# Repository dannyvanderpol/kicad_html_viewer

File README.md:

# kicad_html_viewer
Viewer for viewing KiCad designs in a HTML page

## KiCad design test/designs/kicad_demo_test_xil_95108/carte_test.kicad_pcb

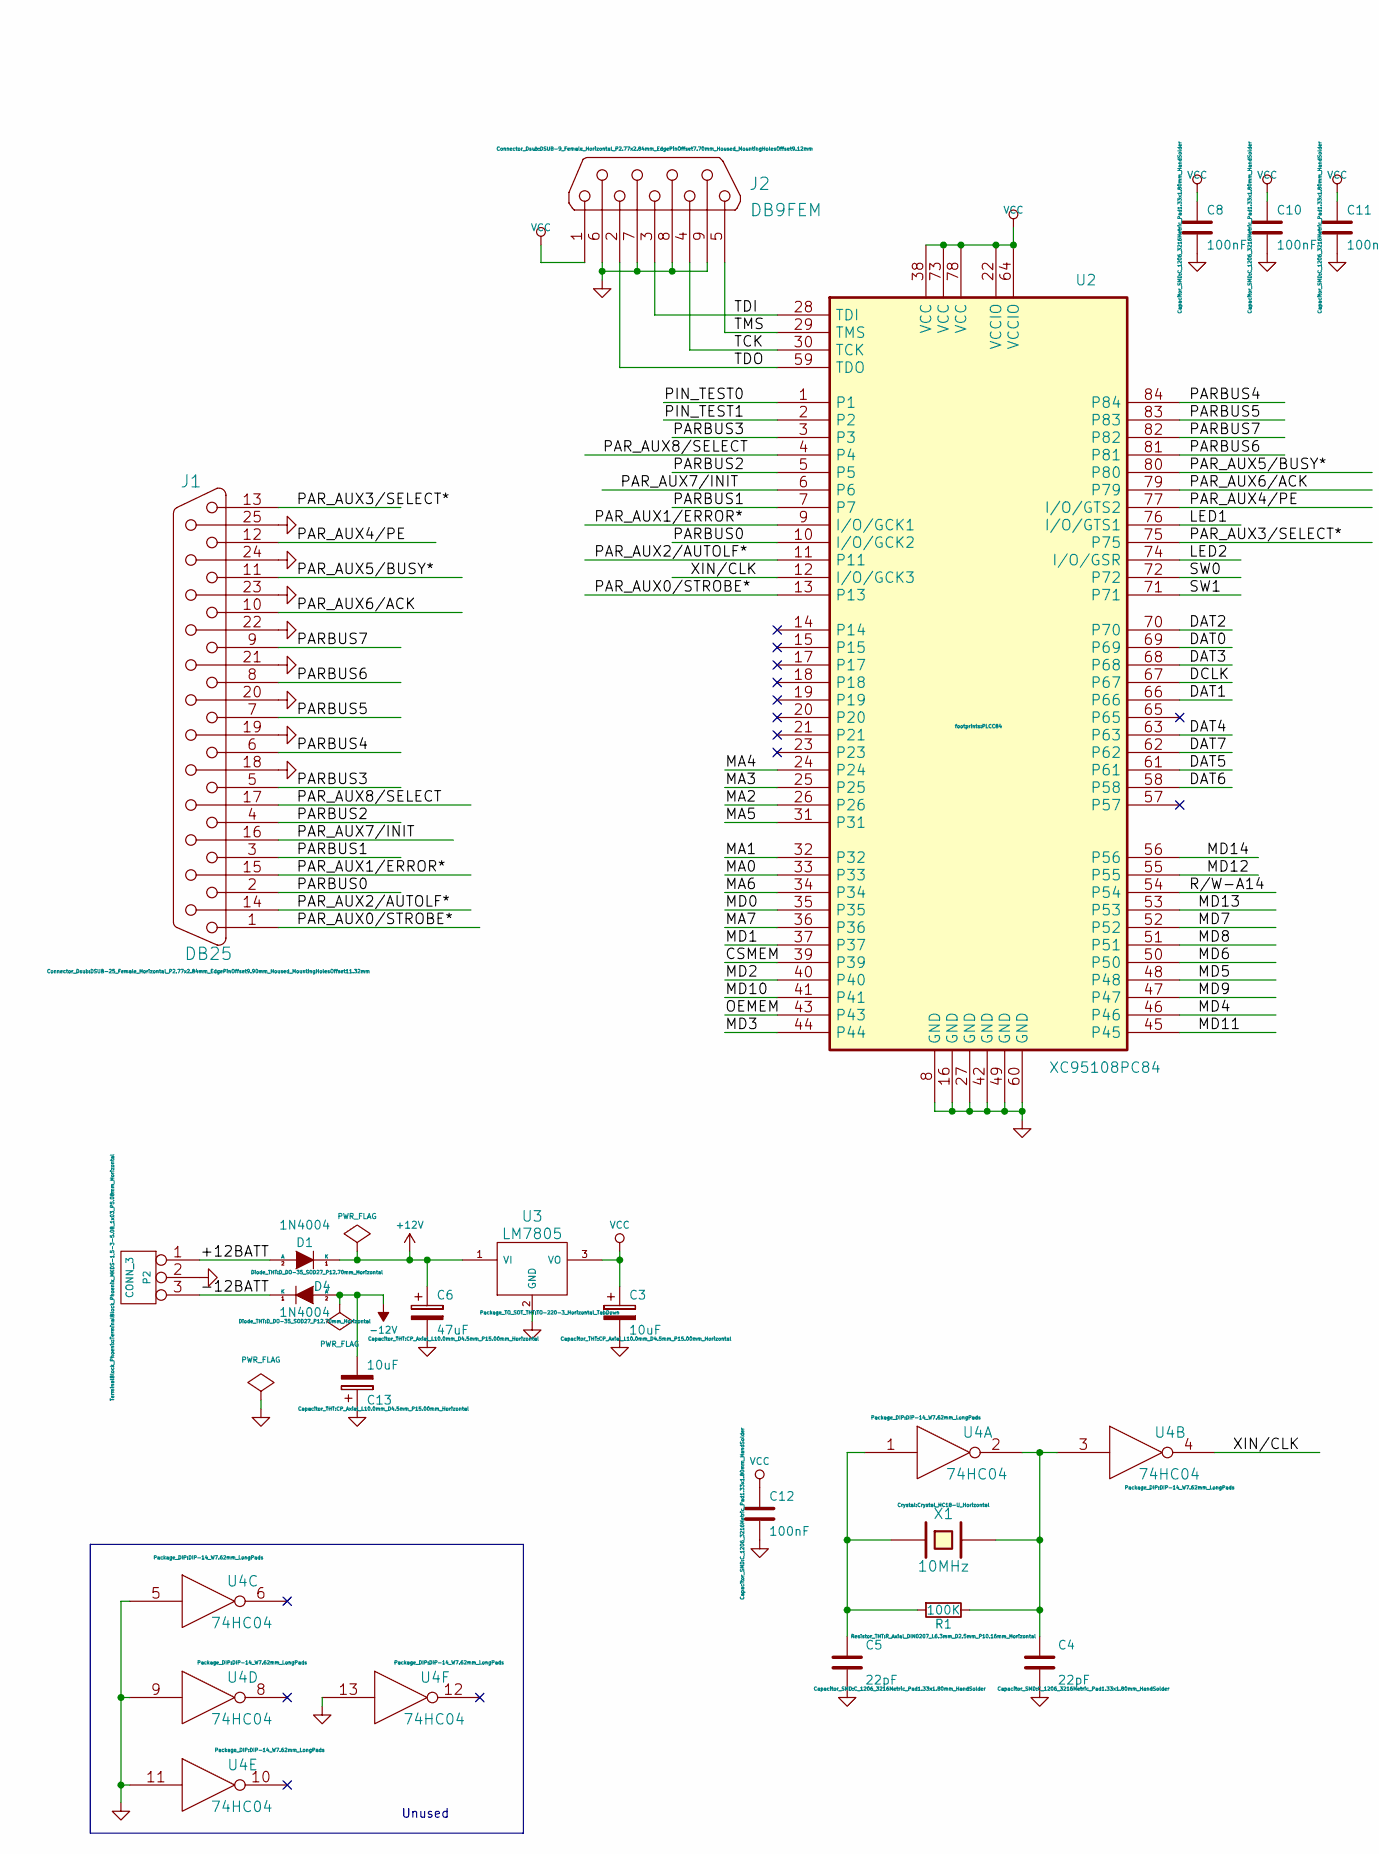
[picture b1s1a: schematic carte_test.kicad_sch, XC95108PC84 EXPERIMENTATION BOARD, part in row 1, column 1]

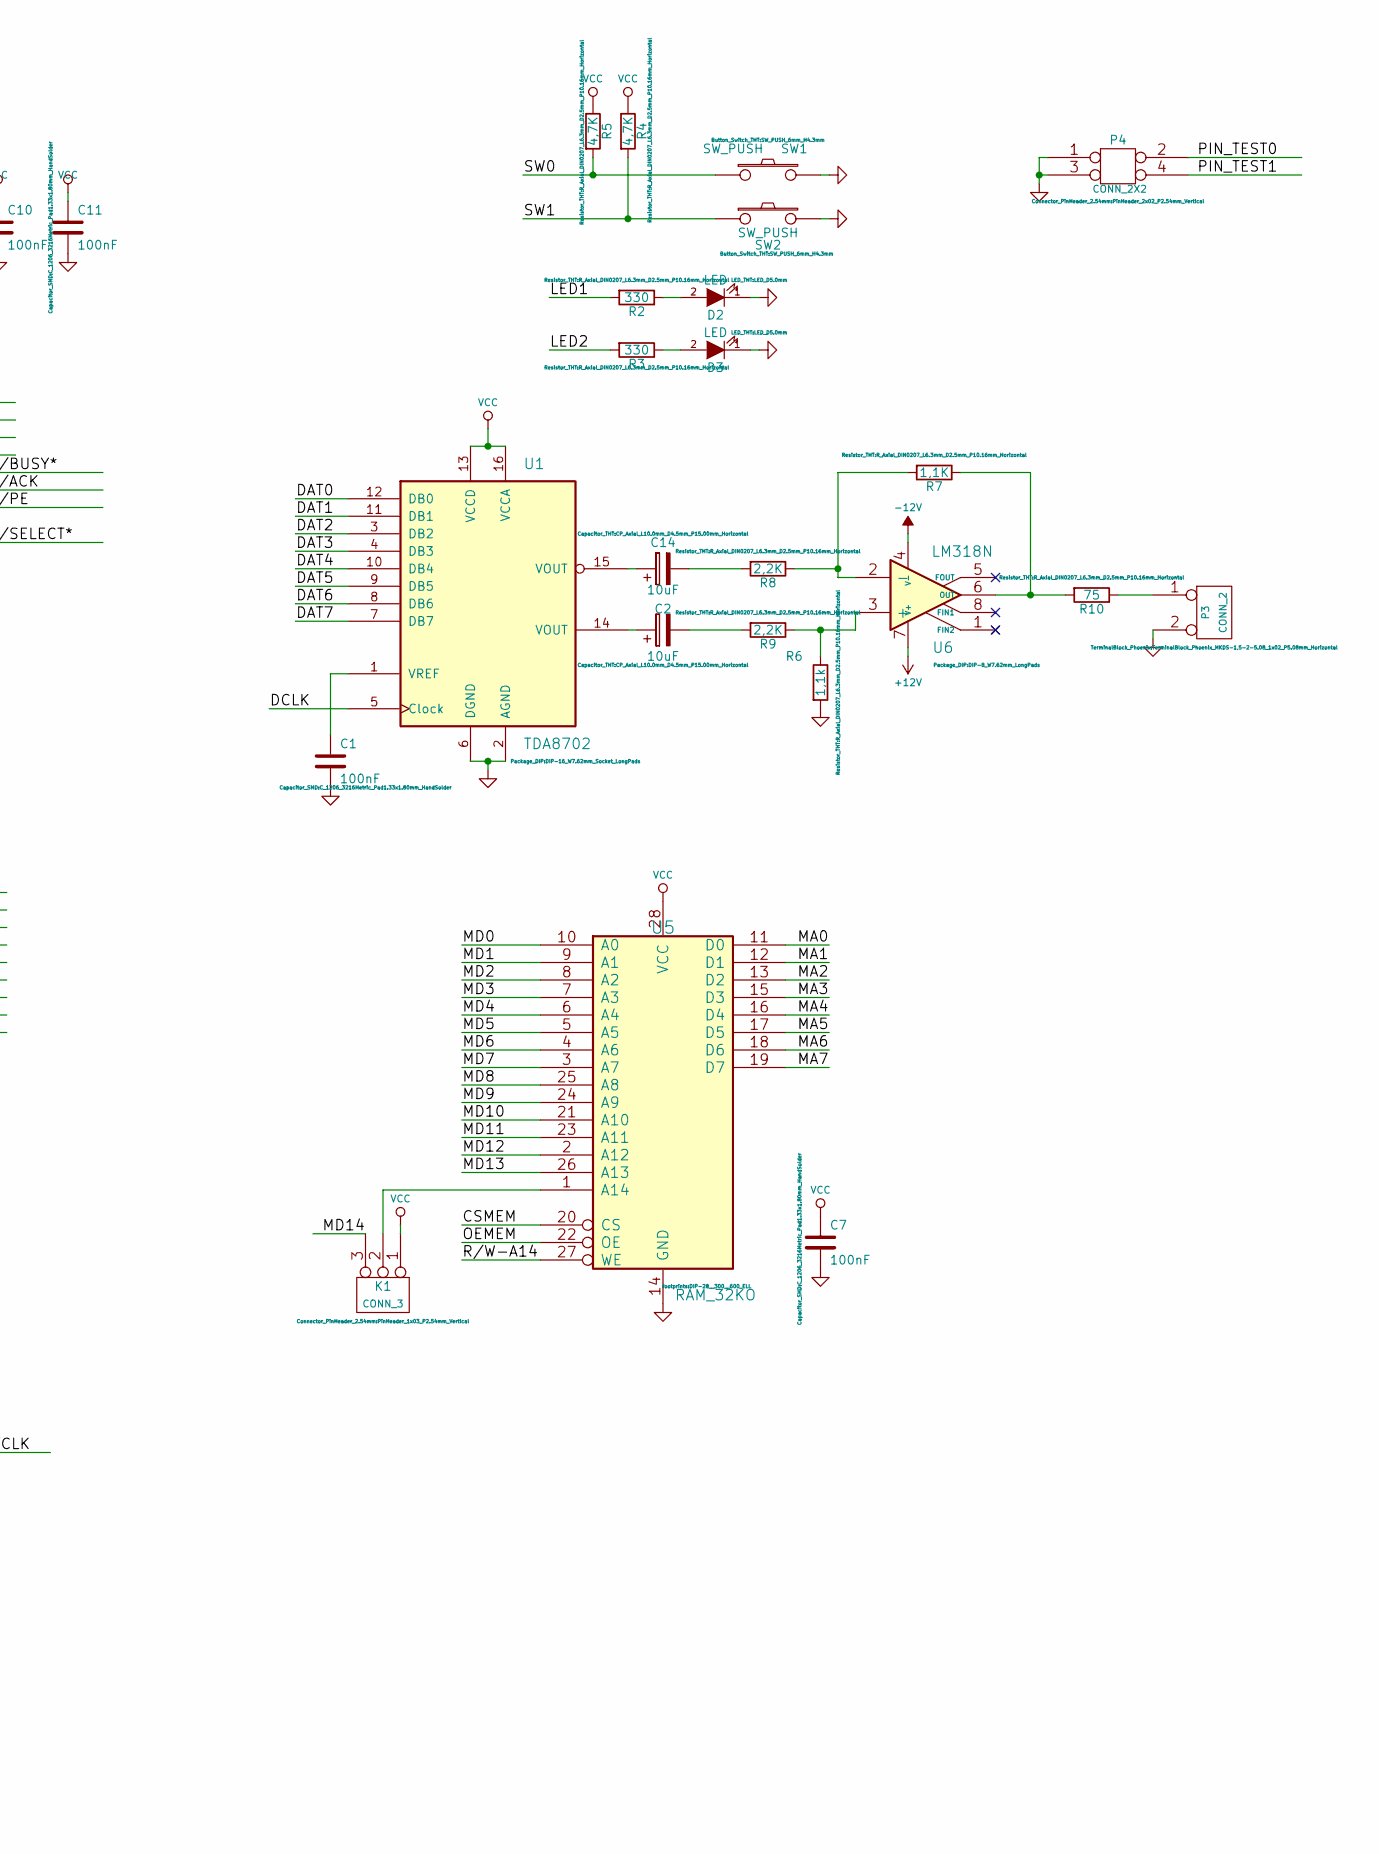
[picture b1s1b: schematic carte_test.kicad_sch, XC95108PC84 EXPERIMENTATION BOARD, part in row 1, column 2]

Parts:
C1, C7, C8, C10, C11, C12: 100nF; C_1206_3216Metric_Pad1.33x1.80mm_HandSolder
C2, C3, C13, C14: 10uF; CP_Axial_L10.0mm_D4.5mm_P15.00mm_Horizontal
C4, C5: 22pF; C_1206_3216Metric_Pad1.33x1.80mm_HandSolder
C6: 47uF; CP_Axial_L10.0mm_D4.5mm_P15.00mm_Horizontal
D1, D4: 1N4004; D_DO-35_SOD27_P12.70mm_Horizontal
D2, D3: LED; LED_D5.0mm
J1: DB25; DSUB-25_Female_Horizontal_P2.77x2.84mm_EdgePinOffset9.90mm_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
J2: DB9FEM; DSUB-9_Female_Horizontal_P2.77x2.84mm_EdgePinOffset7.70mm_H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
K1: CONN_3; PinHeader_1x03_P2.54mm_Vertical
P2: CONN_3; TerminalBlock_Phoenix_MKDS-1,5-3-5.08_1x03_P5.08mm_Horizont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
P3: CONN_2; TerminalBlock_Phoenix_MKDS-1,5-2-5.08_1x02_P5.08mm_Horizont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
P4: CONN_2X2; PinHeader_2x02_P2.54mm_Vertical
R1: 100K; R_Axial_DIN0207_L6.3mm_D2.5mm_P10.16mm_Horizontal
R2, R3: 330; R_Axial_DIN0207_L6.3mm_D2.5mm_P10.16mm_Horizontal
R4, R5: 4,7K; R_Axial_DIN0207_L6.3mm_D2.5mm_P10.16mm_Horizontal
R6: 1,1k; R_Axial_DIN0207_L6.3mm_D2.5mm_P10.16mm_Horizontal
R7: 1,1K; R_Axial_DIN0207_L6.3mm_D2.5mm_P10.16mm_Horizontal
R8, R9: 2,2K; R_Axial_DIN0207_L6.3mm_D2.5mm_P10.16mm_Horizontal
R10: 75; R_Axial_DIN0207_L6.3mm_D2.5mm_P10.16mm_Horizontal
SW1, SW2: SW_PUSH; SW_PUSH_6mm_H4.3mm
U1: TDA8702; DIP-16_W7.62mm_Socket_LongPads
U2: XC95108PC84; PLCC84
U3: LM7805; TO-220-3_Horizontal_TabDown
U4: 74HC04; DIP-14_W7.62mm_LongPads
U5: RAM_32KO; DIP-28__300__600_ELL
U6: LM318N; DIP-8_W7.62mm_LongPads
X1: 10MHz; Crystal_HC18-U_Horizontal

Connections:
+12V: C6.1, D1.1 (K), U3.1 (VI), U6.7 (V+)
-12V: C13.2, D4.2 (A), U6.4 (V-)
/+12BATT: D1.2 (A), P2.1
/-12BATT: D4.1 (K), P2.3
/CSMEM: U2.39, U5.20 (CS)
/DAT0: U1.12 (DB0), U2.69
/DAT1: U1.11 (DB1), U2.66
/DAT2: U1.3 (DB2), U2.70
/DAT3: U1.4 (DB3), U2.68
/DAT4: U1.10 (DB4), U2.63
/DAT5: U1.9 (DB5), U2.61
/DAT6: U1.8 (DB6), U2.58
/DAT7: U1.7 (DB7), U2.62
/DCLK: U1.5 (Clock), U2.67
/LED1: R2.2, U2.76 (I/O/GTS1)
/LED2: R3.2, U2.74 (I/O/GSR)
/MA0: U2.33, U5.11 (D0)
/MA1: U2.32, U5.12 (D1)
/MA2: U2.26, U5.13 (D2)
/MA3: U2.25, U5.15 (D3)
/MA4: U2.24, U5.16 (D4)
/MA5: U2.31, U5.17 (D5)
/MA6: U2.34, U5.18 (D6)
/MA7: U2.36, U5.19 (D7)
/MD0: U2.35, U5.10 (A0)
/MD1: U2.37, U5.9 (A1)
/MD2: U2.40, U5.8 (A2)
/MD3: U2.44, U5.7 (A3)
/MD4: U2.46, U5.6 (A4)
/MD5: U2.48, U5.5 (A5)
/MD6: U2.50, U5.4 (A6)
/MD7: U2.52, U5.3 (A7)
/MD8: U2.51, U5.25 (A8)
/MD9: U2.47, U5.24 (A9)
/MD10: U2.41, U5.21 (A10)
/MD11: U2.45, U5.23 (A11)
/MD12: U2.55, U5.2 (A12)
/MD13: U2.53, U5.26 (A13)
/MD14: K1.3, U2.56
/OEMEM: U2.43, U5.22 (OE)
/PARBUS0: J1.2, U2.10 (I/O/GCK2)
/PARBUS1: J1.3, U2.7
/PARBUS2: J1.4, U2.5
/PARBUS3: J1.5, U2.3
/PARBUS4: J1.6, U2.84
/PARBUS5: J1.7, U2.83
/PARBUS6: J1.8, U2.81
/PARBUS7: J1.9, U2.82
/PAR_AUX0/STROBE*: J1.1, U2.13
/PAR_AUX1/ERROR*: J1.15, U2.9 (I/O/GCK1)
/PAR_AUX2/AUTOLF*: J1.14, U2.11
/PAR_AUX3/SELECT*: J1.13, U2.75
/PAR_AUX4/PE: J1.12, U2.77 (I/O/GTS2)
/PAR_AUX5/BUSY*: J1.11, U2.80
/PAR_AUX6/ACK: J1.10, U2.79
/PAR_AUX7/INIT: J1.16, U2.6
/PAR_AUX8/SELECT: J1.17, U2.4
/PIN_TEST0: P4.2, U2.1
/PIN_TEST1: P4.4, U2.2
/R/W-A14: U2.54, U5.27 (WE)
/SW0: R5.2, SW1.1, U2.72
/SW1: R4.2, SW2.1, U2.71
/TCK: J2.4, U2.30 (TCK)
/TDI: J2.3, U2.28 (TDI)
/TDO: J2.2, U2.59 (TDO)
/TMS: J2.5, U2.29 (TMS)
/XIN/CLK: U2.12 (I/O/GCK3), U4.4
GND: C1.2, C3.2, C4.2, C5.2, C6.2, C7.2, C8.2, C10.2, C11.2, C12.2, C13.1, D2.1 (K), D3.1 (K), J1.18, J1.19, J1.20, J1.21, J1.22, J1.23, J1.24, J1.25, J2.6, J2.7, J2.8, J2.9, P2.2 (PM), P3.2 (PM), P4.1, P4.3, R6.2, SW1.2, SW2.2, U1.2 (AGND), U1.6 (DGND), U2.8 (GND), U2.16 (GND), U2.27 (GND), U2.42 (GND), U2.49 (GND), U2.60 (GND), U3.2 (GND), U4.5, U4.7 (GND), U4.9, U4.11, U4.13, U5.14 (GND)
unnamed: C2.1, U1.14 (VOUT)
unnamed: C2.2, R9.2
unnamed: C4.1, R1.1, U4.2, U4.3, X1.2
unnamed: C5.1, R1.2, U4.1, X1.1
unnamed: C14.1, U1.15 (VOUT)
unnamed: C14.2, R8.2
unnamed: D2.2 (A), R2.1
unnamed: D3.2 (A), R3.1
unnamed: K1.2 (PM), U5.1 (A14)
unnamed: P3.1, R10.1
unnamed: C1.1, U1.1 (VREF)
unnamed: R6.1, R9.1, U6.3 (+)
unnamed: R7.2, R8.1, U6.2 (-)
unnamed: R7.1, R10.2, U6.6 (OUT)
VCC: C3.1, C7.1, C8.1, C10.1, C11.1, C12.1, J2.1, K1.1, R4.1, R5.1, U1.13 (VCCD), U1.16 (VCCA), U2.22 (VCCIO), U2.38 (VCC), U2.64 (VCCIO), U2.73 (VCC), U2.78 (VCC), U3.3 (VO), U4.14 (VCC), U5.28 (VCC)

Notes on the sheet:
Unused

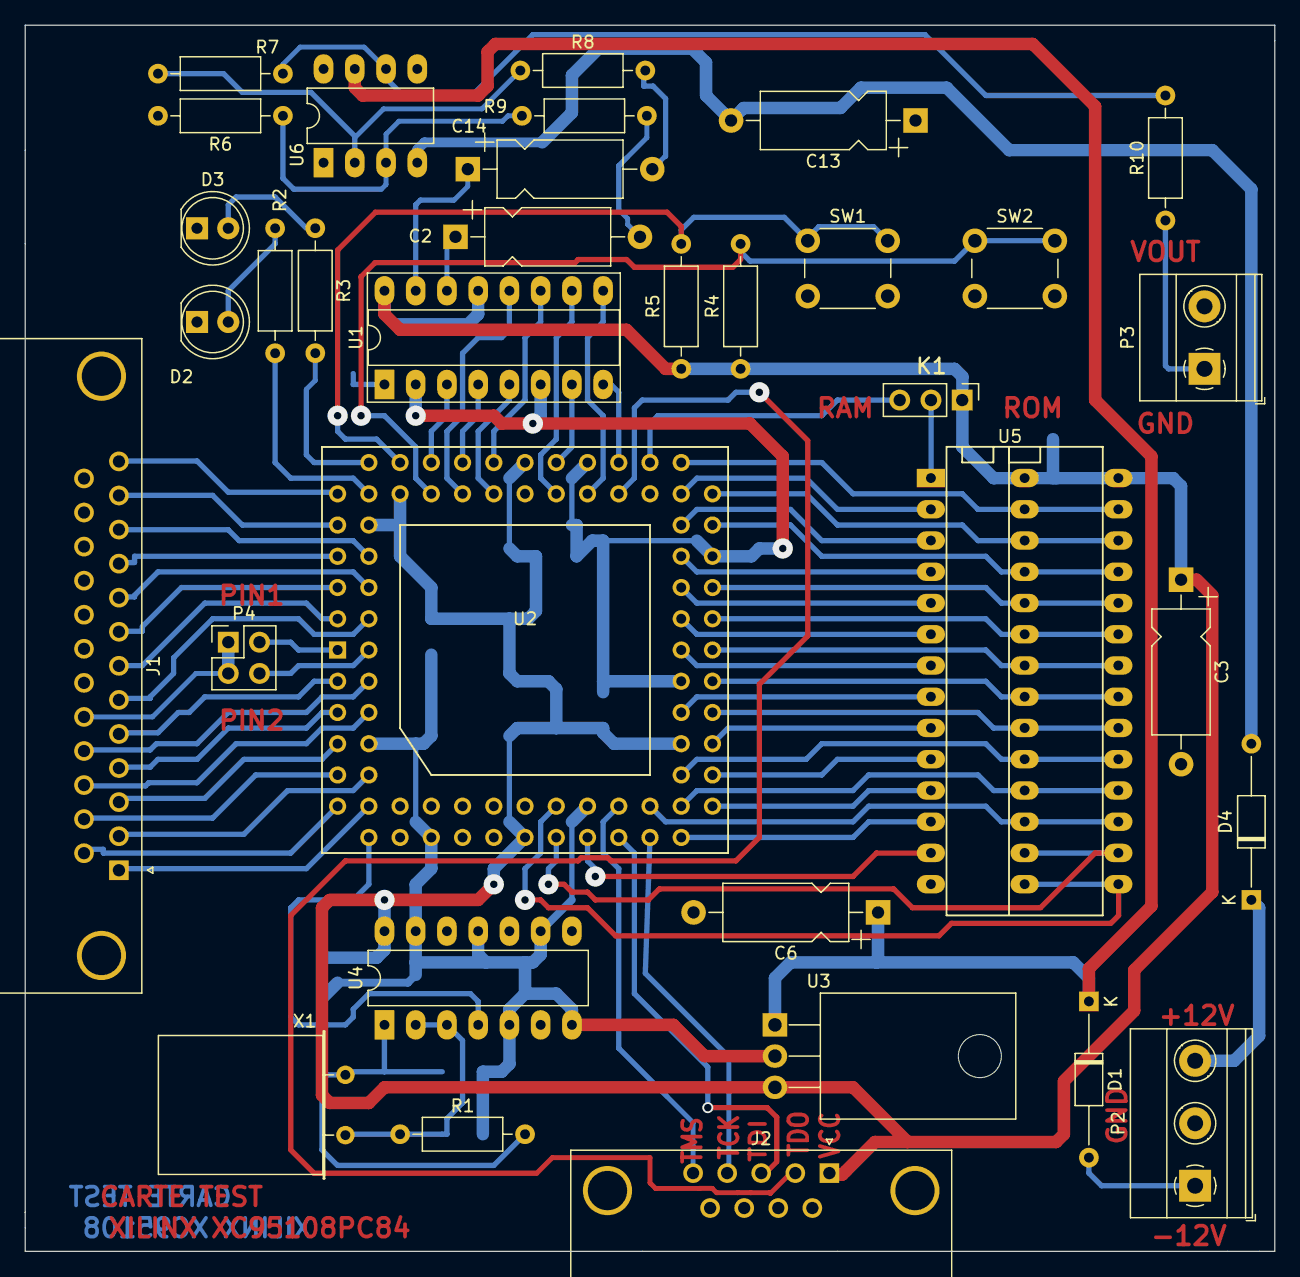
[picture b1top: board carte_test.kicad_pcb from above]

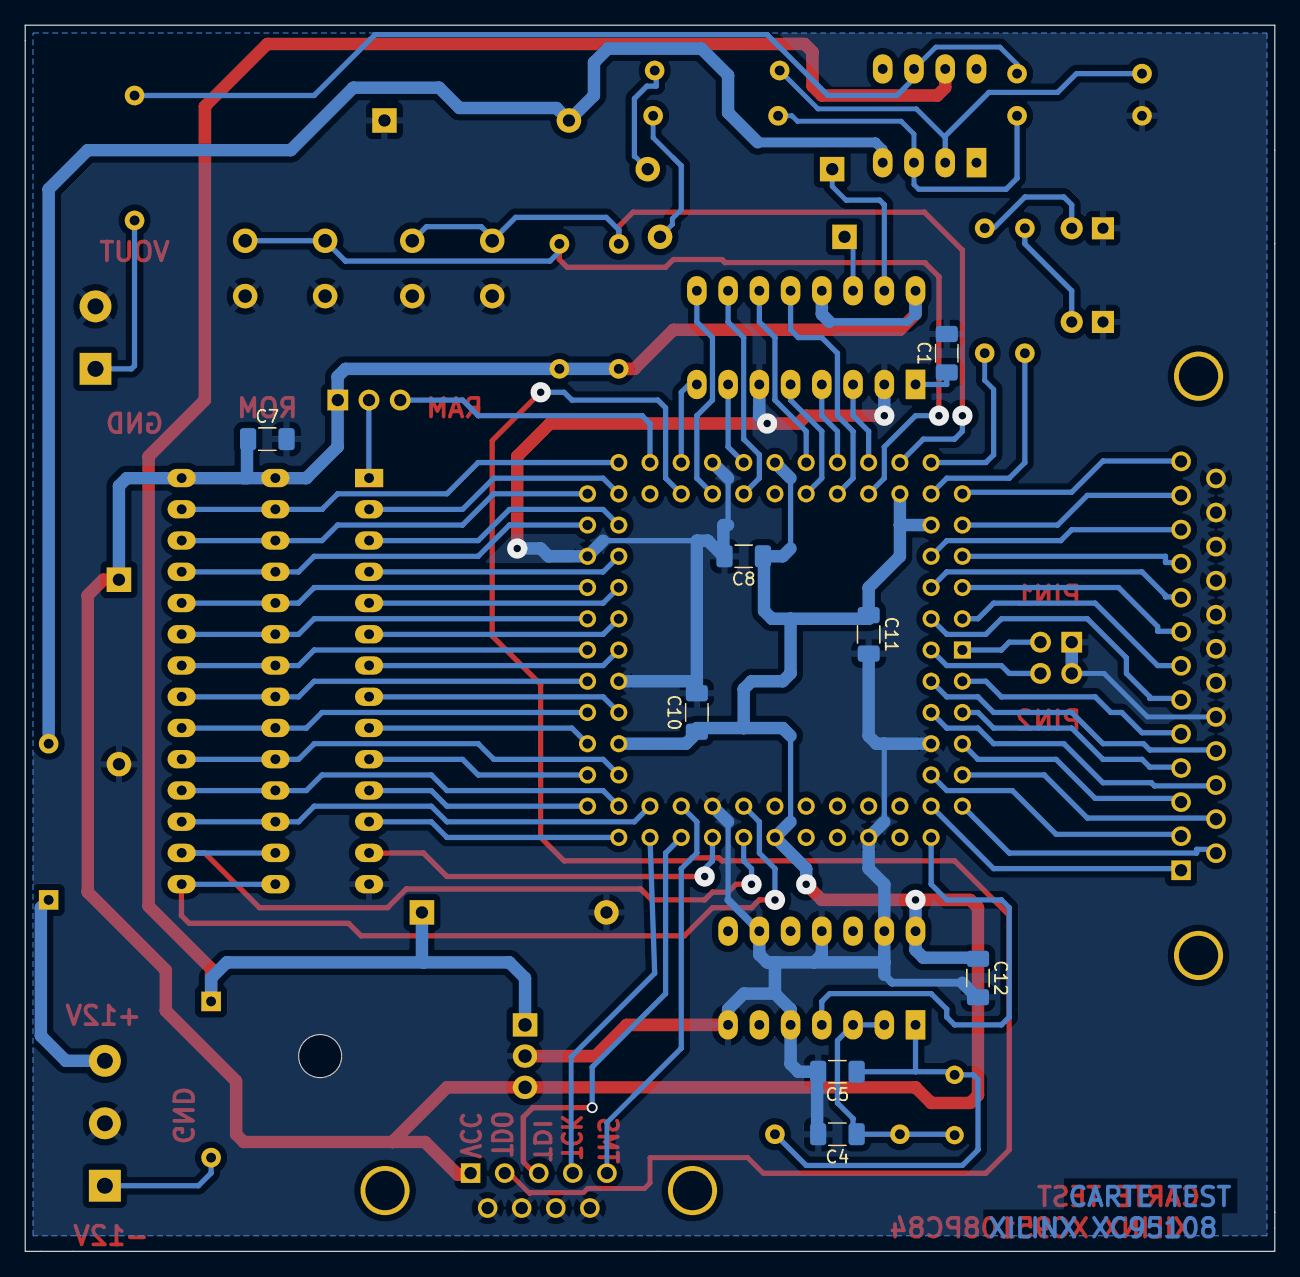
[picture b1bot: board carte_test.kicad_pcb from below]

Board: 2 copper layers, 101.6 x 99.7 mm, 42 parts (8 on the bottom side), 83 nets.

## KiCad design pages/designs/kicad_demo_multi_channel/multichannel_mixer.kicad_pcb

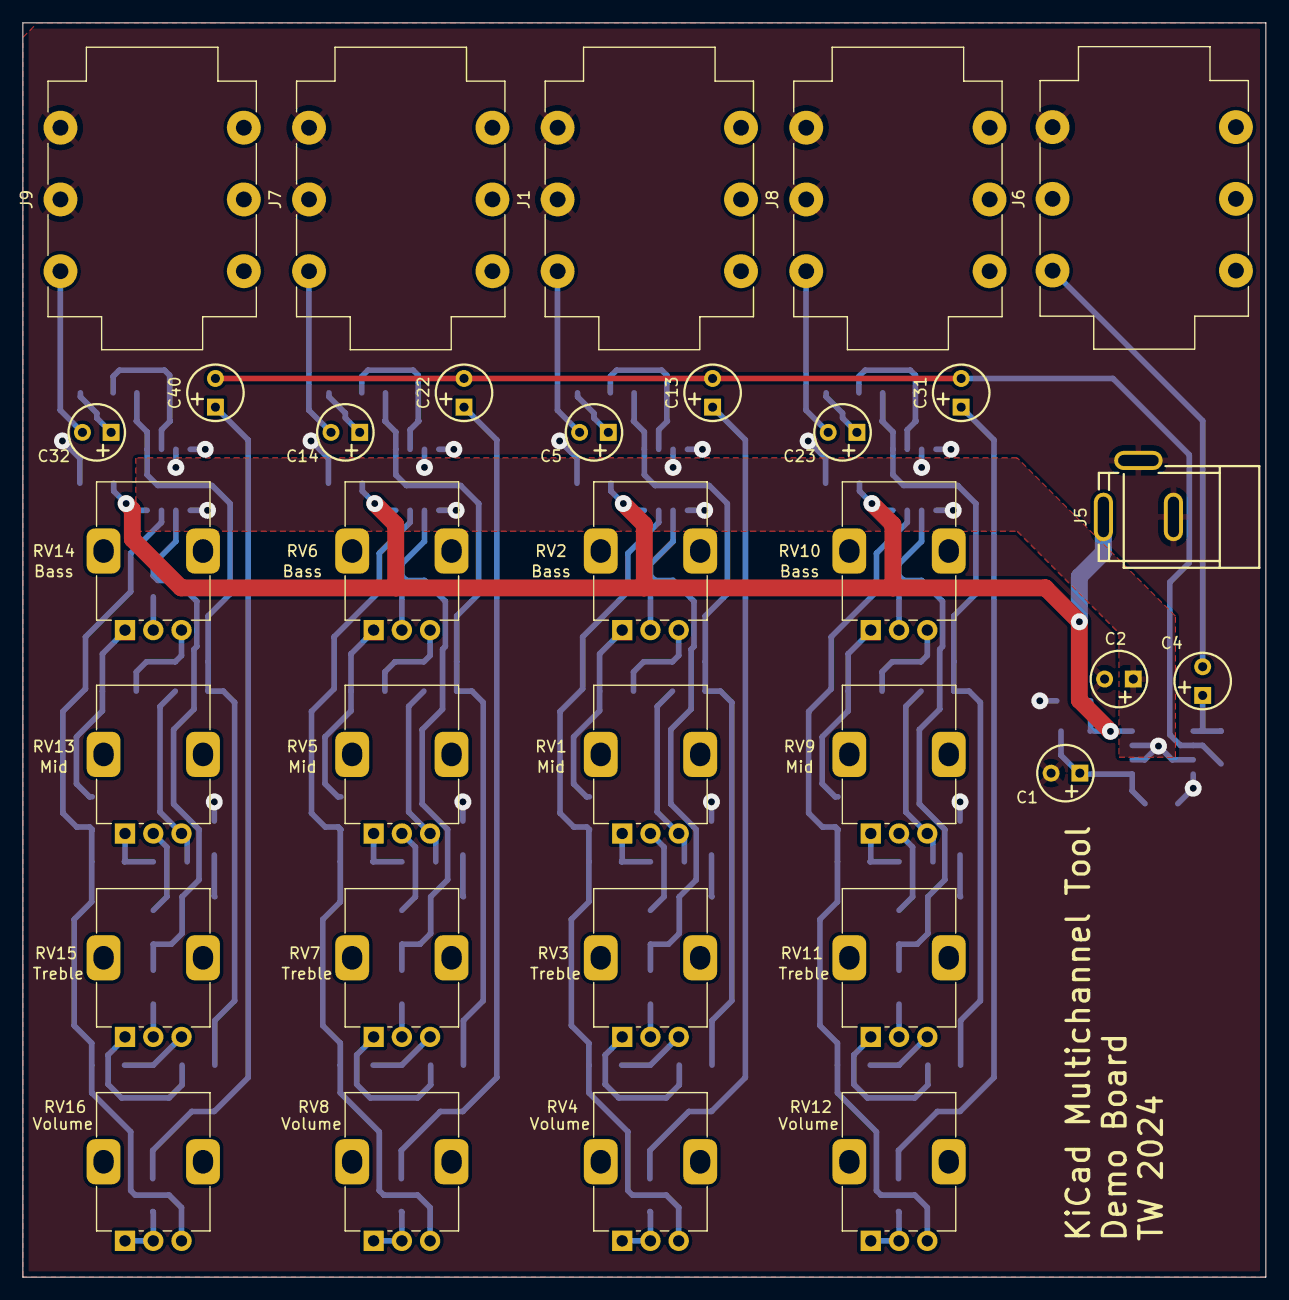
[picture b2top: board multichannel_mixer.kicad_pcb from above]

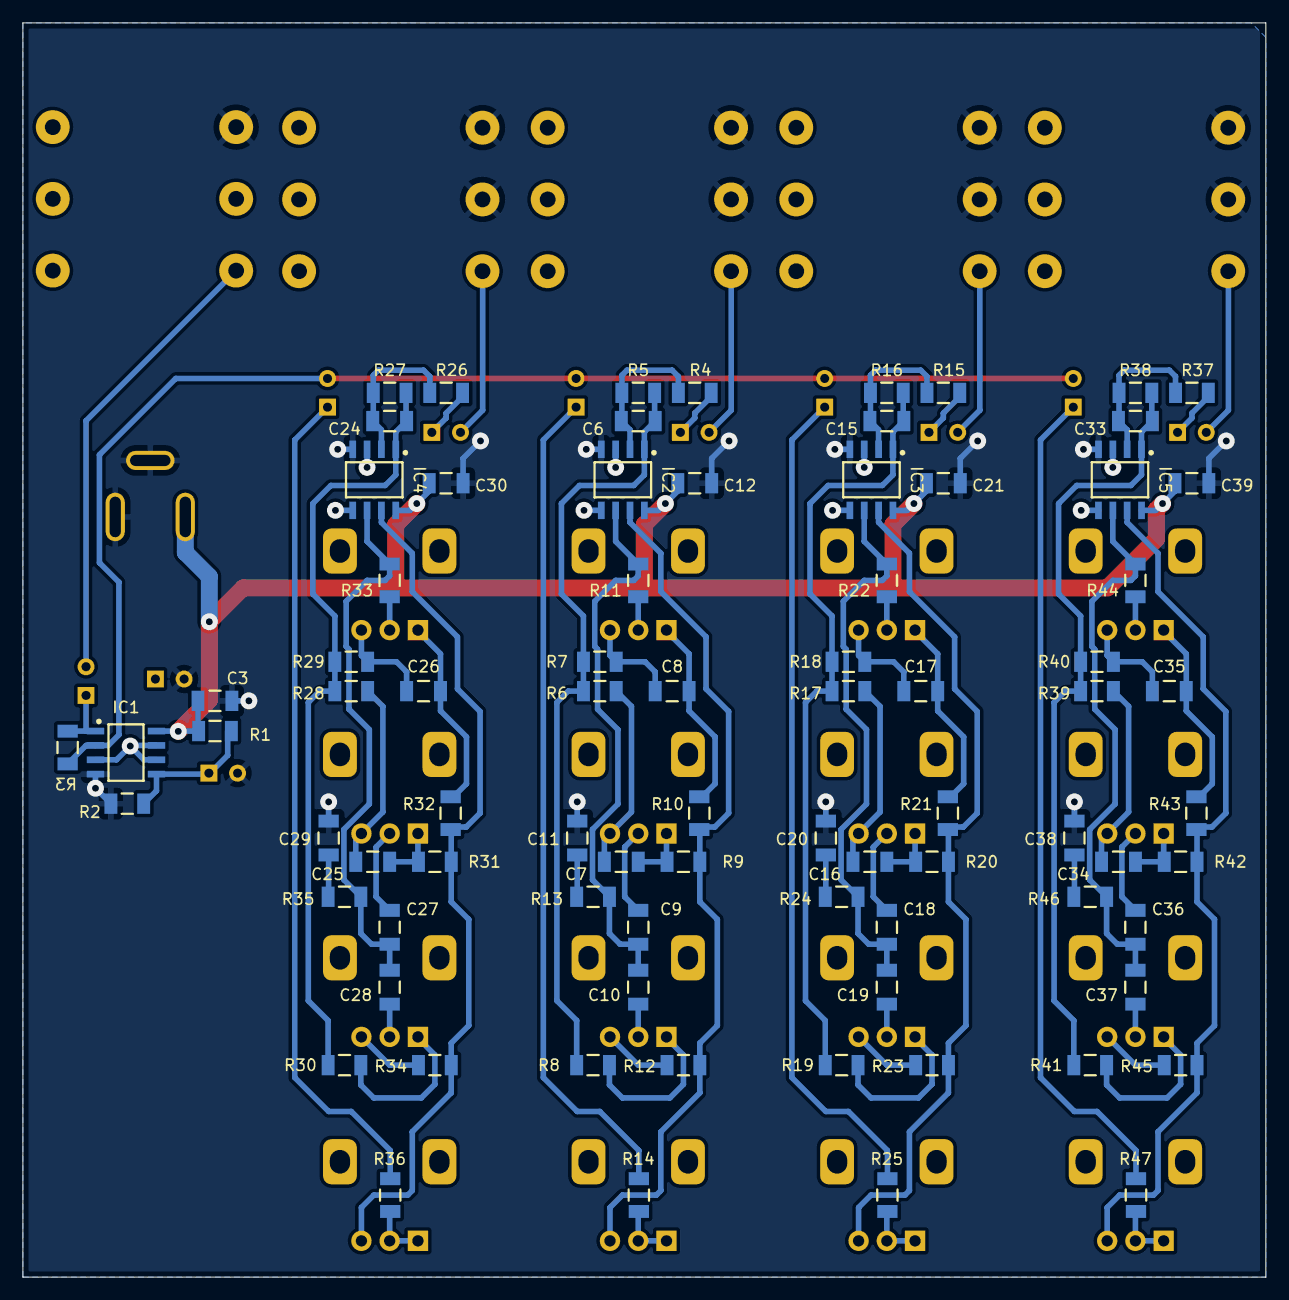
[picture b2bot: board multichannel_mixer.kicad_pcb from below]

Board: 2 copper layers, 110.0 x 111.0 mm, 114 parts (81 on the bottom side), 79 nets.

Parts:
C1, C2, C4, C5, C13, C14, C22, C23, C31, C32, C40: CTEB_2.2UF_35V_10%_254-500X840; CAPPRB254-500X840
C3, C6, C7, C8, C9, C10, C11, C12, C15, C16, C17, C18, C19, C20, C21, C24, C25, C26, C27, C28, C29, C30, C33, C34, C35, C36, C37, C38, C39: CC1206_100NF_50V_10%_X7R; CAPC3216X140N
IC1, IC2, IC3, IC4, IC5: TL072CD; SOIC127P600X175-8N
J1, J6, J7, J8, J9: CH1; Jack_6.35mm_Neutrik_NMJ6HCD2_Horizontal
J5: Power; CLIFF_FC68148(DC-10A)
R1, R2, R3, R4, R5, R6, R7, R8, R9, R10, R11, R12, R13, R14, R15, R16, R17, R18, R19, R20, R21, R22, R23, R24, R25, R26, R27, R28, R29, R30, R31, R32, R33, R34, R35, R36, R37, R38, R39, R40, R41, R42, R43, R44, R45, R46, R47: R1206_10K_1%_0.25W_100PPM; RESC3216X65N
RV1, RV5, RV9, RV13: Mid; Potentiometer_Alps_RK09K_Single_Vertical
RV2, RV6, RV10, RV14: Bass; Potentiometer_Alps_RK09K_Single_Vertical
RV3, RV7, RV11, RV15: Treble; Potentiometer_Alps_RK09K_Single_Vertical
RV4, RV8, RV12, RV16: Volume; Potentiometer_Alps_RK09K_Single_Vertical

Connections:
+12V: C3.2, C12.2, C21.2, C30.2, C39.2, IC1.8 (V+), IC2.8 (V+), IC3.8 (V+), IC4.8 (V+), IC5.8 (V+), J5.1, R1.2
/CH1/OUT: C13.2, C22.2, C31.2, C40.2, IC1.2 (IN-), R3.1
GND: C1.2, C2.2, C3.1, C11.1, C12.1, C20.1, C21.1, C29.1, C30.1, C38.1, C39.1, IC1.4 (V-), IC2.4 (V-), IC3.4 (V-), IC4.4 (V-), IC5.4 (V-), J1.R, J1.S, J5.2, J5.3, J6.S, J7.R, J7.S, J8.R, J8.S, J9.R, J9.S, R2.1
unnamed: C4.2, J6.T
unnamed: C5.1, R4.1
unnamed: C5.2, J1.T
unnamed: C7.1, R6.2, RV1.3
unnamed: C7.2, R9.1, RV1.1
unnamed: C8.1, R7.2, RV2.3
unnamed: C8.2, R10.1, RV2.1
unnamed: C9.1, RV1.2
unnamed: C10.1, RV3.2
unnamed: C11.2, R13.1
unnamed: C13.1, R14.2
unnamed: C14.1, R15.1
unnamed: C14.2, J7.T
unnamed: C16.1, R17.2, RV5.3
unnamed: C16.2, R20.1, RV5.1
unnamed: C17.1, R18.2, RV6.3
unnamed: C17.2, R21.1, RV6.1
unnamed: C18.1, RV5.2
unnamed: C19.1, RV7.2
unnamed: C20.2, R24.1
unnamed: C22.1, R25.2
unnamed: C23.1, R26.1
unnamed: C23.2, J8.T
unnamed: C25.1, R28.2, RV9.3
unnamed: C25.2, R31.1, RV9.1
unnamed: C26.1, R29.2, RV10.3
unnamed: C26.2, R32.1, RV10.1
unnamed: C27.1, RV9.2
unnamed: C28.1, RV11.2
unnamed: C29.2, R35.1
unnamed: C31.1, R36.2
unnamed: C32.1, R37.1
unnamed: C32.2, J9.T
unnamed: C34.1, R39.2, RV13.3
unnamed: C34.2, R42.1, RV13.1
unnamed: C35.1, R40.2, RV14.3
unnamed: C35.2, R43.1, RV14.1
unnamed: C36.1, RV13.2
unnamed: C37.1, RV15.2
unnamed: C38.2, R46.1
unnamed: C40.1, R47.2
unnamed: C4.1, IC1.1 (OUT), R3.2
unnamed: C1.1, IC1.5 (IN+), R1.1, R2.2
unnamed: C6.1, IC2.2 (IN-), R4.2, R5.1
unnamed: C6.2, IC2.1 (OUT), R5.2, R6.1, R7.1, R8.2
unnamed: C9.2, C10.2, IC2.6 (IN-), R11.2, R13.2
unnamed: IC2.7 (OUT), R9.2, R10.2, R12.1, RV4.3
unnamed: C15.1, IC3.2 (IN-), R15.2, R16.1
unnamed: C15.2, IC3.1 (OUT), R16.2, R17.1, R18.1, R19.2
unnamed: C18.2, C19.2, IC3.6 (IN-), R22.2, R24.2
unnamed: IC3.7 (OUT), R20.2, R21.2, R23.1, RV8.3
unnamed: C24.1, IC4.2 (IN-), R26.2, R27.1
unnamed: C24.2, IC4.1 (OUT), R27.2, R28.1, R29.1, R30.2
unnamed: C27.2, C28.2, IC4.6 (IN-), R33.2, R35.2
unnamed: IC4.7 (OUT), R31.2, R32.2, R34.1, RV12.3
unnamed: C33.1, IC5.2 (IN-), R37.2, R38.1
unnamed: C33.2, IC5.1 (OUT), R38.2, R39.1, R40.1, R41.2
unnamed: C36.2, C37.2, IC5.6 (IN-), R44.2, R46.2
unnamed: IC5.7 (OUT), R42.2, R43.2, R45.1, RV16.3
unnamed: R8.1, RV3.1
unnamed: R11.1, RV2.2
unnamed: R12.2, RV3.3
unnamed: R14.1, RV4.1, RV4.2
unnamed: R19.1, RV7.1
unnamed: R22.1, RV6.2
unnamed: R23.2, RV7.3
unnamed: R25.1, RV8.1, RV8.2
unnamed: R30.1, RV11.1
unnamed: R33.1, RV10.2
unnamed: R34.2, RV11.3
unnamed: R36.1, RV12.1, RV12.2
unnamed: R41.1, RV15.1
unnamed: R44.1, RV14.2
unnamed: R45.2, RV15.3
unnamed: R47.1, RV16.1, RV16.2
vbias: C2.1, IC1.3 (IN+), IC1.6 (IN-), IC1.7 (OUT), IC2.3 (IN+), IC2.5 (IN+), IC3.3 (IN+), IC3.5 (IN+), IC4.3 (IN+), IC4.5 (IN+), IC5.3 (IN+), IC5.5 (IN+)

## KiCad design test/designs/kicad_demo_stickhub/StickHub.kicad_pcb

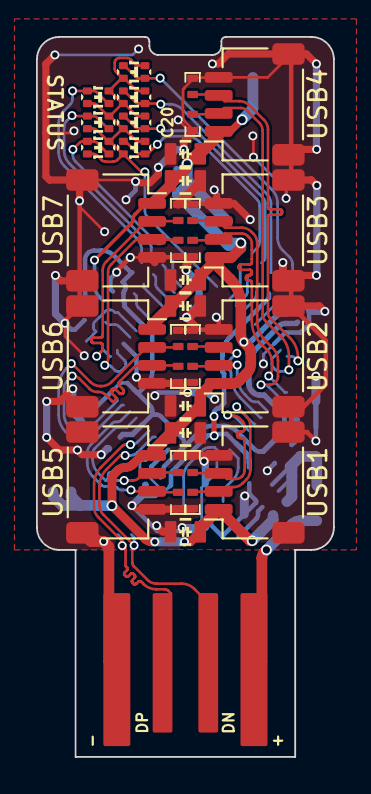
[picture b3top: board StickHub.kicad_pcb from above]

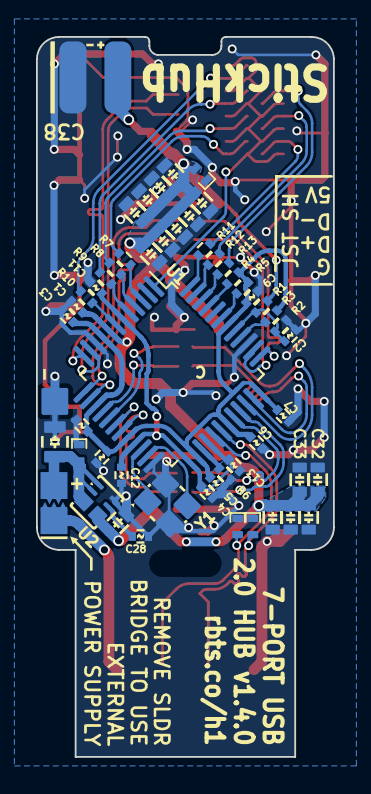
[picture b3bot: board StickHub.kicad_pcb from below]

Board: 2 copper layers, 16.5 x 40.0 mm, 94 parts (57 on the bottom side), 45 nets.

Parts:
C1: 1uF 10V; 1005_C
C2, C5, C6, C7, C8, C9, C10, C11, C12, C13: 0.1uF; 1005_C
C3, C4: 10uF 6.3V; 1005_C
C14, C15, C16, C17, C18, C19, C20, C21: 0.1uF 100V; 2012_C
C22, C23, C24, C25, C26, C27, C29, C30, C31, C32, C33, C34, C35, C36, C37: 22uF 10V; 1608_C
C28: 15nF; 1005_C
C38: 330uF 10V; CP_Elec_6.3x11_Board_Edge_Mirrored
D1, D2, D3, D4, D5, D6, D7, D8, D9, D10, D11, D12, D13, D14, D22, D23: TVS; D_0402
D15, D16, D17, D18, D19, D20, D21: USB; Duo_LED_1.6x0.8_Kingbright_APHB1608LZGKSURKC
D24, D25: 5V; D_0402
H1: Strap; Plain_Hole_3mm
J1: HOST; USB_A_PCB_traces_small
J2: USB1; JST_SH_SM04B-SRSS-TB_1x04-1MP_P1.00mm_Horizontal
J3: USB2; JST_SH_SM04B-SRSS-TB_1x04-1MP_P1.00mm_Horizontal
J4: USB3; JST_SH_SM04B-SRSS-TB_1x04-1MP_P1.00mm_Horizontal
J5: USB4; JST_SH_SM04B-SRSS-TB_1x04-1MP_P1.00mm_Horizontal
J6: USB5; JST_SH_SM04B-SRSS-TB_1x04-1MP_P1.00mm_Horizontal
J7: USB6; JST_SH_SM04B-SRSS-TB_1x04-1MP_P1.00mm_Horizontal
J8: USB7; JST_SH_SM04B-SRSS-TB_1x04-1MP_P1.00mm_Horizontal
J9: EXTGND; 1P-1.5x1.5
JP1: EXTPWR; JP-2_1.5x1.5
LOGO1: Logo; Creative_Commons_CC_Mask
LOGO2: Logo; Creative_Commons_BY_Mask
LOGO3: Logo; Creative_Commons_NC_Mask
LOGO4: Logo; Creative_Commons_SA_Mask
R1: 10k; R_1005_C
R2, R3, R4, R5: 100k; R_1005_C
R6: 2.7k; R_1005_C
R7, R8, R9, R10, R11, R12, R13: 470; R_1005_C
U1: MaxLinear_XR22417-48; LQFP-48_7x7mm_P0.5mm
U2: Dialog_SLG5NT1487V; TDFN-8_1.5x2mm_Fused-Lead_JEDEC_MO-252_W2015D
Y1: 12MHz 50ppm 16-20pF; Crystal_4-SMD_2.5x2mm

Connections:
+1V8: C4.1, C11.1, C12.1, C13.1, U1.6 (VCC18), U1.21 (VCC18), U1.25 (1V8_OUT), U1.28 (VCC18)
+3.3V: C3.1, C5.1, C6.1, C7.1, C8.1, C9.1, C10.1, R3.1, R4.1, R5.1, U1.9 (3V3_OUT), U1.15 (VCC33), U1.20 (VCC33), U1.26 (VCC33), U1.31 (VCC33), U1.36 (VCC33), U1.42 (VCC33)
+5V: C1.1, C14.1, C15.1, C16.1, C17.1, C18.1, C19.1, C20.1, C22.1, C23.1, C24.1, C25.1, C26.1, C27.1, C29.1, C30.1, C31.1, C32.1, C33.1, C34.1, C35.1, C36.1, C37.1, C38.1 (+), D25.2 (A2), J2.1, J3.1, J4.1, J5.1, J6.1, J7.1, J8.1, R1.1, U1.8 (VCC5), U2.5 (S)
/D+: D23.2 (A2), J1.3, U1.30 (UP_D+)
/D-: D22.2 (A2), J1.2, U1.29 (UP_D-)
/LC: D15.GK (2), D15.RA (3), D16.GK (2), D16.RA (3), D17.GK (2), D17.RA (3), D18.GK (2), D18.RA (3), D19.GK (2), D19.RA (3), D20.GK (2), D20.RA (3), D21.GK (2), D21.RA (3), U1.1 (LED_CTL)
/LED1: R7.2, U1.3 (LED1/SCL)
/LED2: R8.2, U1.4 (LED2)
/LED3: R9.2, U1.5 (LED3)
/LED4: R10.2, U1.7 (LED4)
/LED5: R11.2, U1.48 (LED5)
/LED6: R12.2, U1.47 (LED6)
/LED7: R13.2, U1.46 (LED7)
/U1D+: D2.2 (A2), J2.3, U1.19 (USB1D+)
/U1D-: D1.2 (A2), J2.2, U1.18 (USB1D-)
/U2D+: D4.2 (A2), J3.3, U1.17 (USB2D+)
/U2D-: D3.2 (A2), J3.2, U1.16 (USB2D-)
/U3D+: D6.2 (A2), J4.3, U1.14 (USB3D+)
/U3D-: D5.2 (A2), J4.2, U1.13 (USB3D-)
/U4D+: D8.2 (A2), J5.3, U1.12 (USB4D+)
/U4D-: D7.2 (A2), J5.2, U1.11 (USB4D-)
/U5D+: D10.2 (A2), J6.3, U1.33 (USB5D+)
/U5D-: D9.2 (A2), J6.2, U1.32 (USB5D-)
/U6D+: D12.2 (A2), J7.3, U1.35 (USB6D+)
/U6D-: D11.2 (A2), J7.2, U1.34 (USB6D-)
/U7D+: D14.2 (A2), J8.3, U1.38 (USB7D+)
/U7D-: D13.2 (A2), J8.2, U1.37 (USB7D-)
/XI: U1.22 (XTALIN), Y1.1
/XO: U1.23 (XTALOUT), Y1.3
GND: C1.2, C2.2, C3.2, C4.2, C5.2, C6.2, C7.2, C8.2, C9.2, C10.2, C11.2, C12.2, C13.2, C14.2, C15.2, C16.2, C17.2, C18.2, C19.2, C20.2, C21.2, C22.2, C23.2, C24.2, C25.2, C26.2, C27.2, C28.2, C29.2, C30.2, C31.2, C32.2, C33.2, C34.2, C35.2, C36.2, C37.2, C38.2 (-), D1.1 (A1), D2.1 (A1), D3.1 (A1), D4.1 (A1), D5.1 (A1), D6.1 (A1), D7.1 (A1), D8.1 (A1), D9.1 (A1), D10.1 (A1), D11.1 (A1), D12.1 (A1), D13.1 (A1), D14.1 (A1), D22.1 (A1), D23.1 (A1), D24.1 (A1), D25.1 (A1), J1.4, J2.4, J2.MP (MountPin), J3.4, J3.MP (MountPin), J4.4, J4.MP (MountPin), J5.4, J5.MP (MountPin), J6.4, J6.MP (MountPin), J7.4, J7.MP (MountPin), J8.4, J8.MP (MountPin), J9.1, R2.2, R6.2, U1.10 (GND), U1.24 (GND), U1.39 (GND), U2.8 (GND), Y1.2 (GND), Y1.4 (GND)
unnamed: D15.GA (1), D15.RK (4), R7.1
unnamed: D16.GA (1), D16.RK (4), R8.1
unnamed: D17.GA (1), D17.RK (4), R9.1
unnamed: D18.GA (1), D18.RK (4), R10.1
unnamed: D19.GA (1), D19.RK (4), R11.1
unnamed: D20.GA (1), D20.RK (4), R12.1
unnamed: D21.GA (1), D21.RK (4), R13.1
unnamed: J1.1, JP1.1
unnamed: R3.2, U1.40 (EXT_RST#)
unnamed: R6.1, U1.27 (REXT)
unnamed: R5.2, U1.43 (TEST1#)
unnamed: R4.2, U1.45 (TEST3#)
unnamed: C2.1, R1.2, R2.1, U1.41 (VBUS_SENSE)
unnamed: C28.1, U2.7 (CAP)
VIN: C21.1, D24.2 (A2), JP1.2, U2.1 (VDD), U2.2 (ON), U2.3 (D)

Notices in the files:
parts and their libraries:
License: This work is licensed under the Creative Commons CC-BY-SA 4.0 License. To the extent that circuit schematics that use Licensed Material can be considered to be ‘Adapted Material’, then the copyright holder waives article 3.b of the license with respect to these schematics.
